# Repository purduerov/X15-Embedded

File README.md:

# X15-Embedded

Embedded code for the ESCs, solenoids, bricks, and more using CAN communication.

This code is developed with [STM32CubeIDE](https://www.st.com/en/development-tools/stm32cubeide.html)
for the [STM32F042K6T6](https://www.st.com/content/ccc/resource/technical/document/datasheet/52/ad/d0/80/e6/be/40/ad/DM00105814.pdf/files/DM00105814.pdf/jcr:content/translations/en.DM00105814.pdf).
See the [F0 reference manual](https://www.st.com/resource/en/reference_manual/dm00031936-stm32f0x1stm32f0x2stm32f0x8-advanced-armbased-32bit-mcus-stmicroelectronics.pdf) too.

## Building and generating code
Driver code is not tracked by git. To get it, open the IOC file for the project
and go to Project > Generate Code. This will produce the appropriate Driver/ folders
for the code.

## More info
See the [References folder](References) for information on usual setups and
the [common folder](common) for information on setting up the shared implementations
and the shared source files themselves. The [Python folder](Python) has code for testing
and a guide for doing so.

### Recommended settings
##### Optimization
Set optimization for Release builds to -03 rather than -Osize (the default). This setting is in
Project > Properties > C/C++ Build > Settings > Tool Settings > MCU GCC Compiler > Optimization.
This should only be done for Release builds. Debug builds should not be optimization

##### Whitespace
In Window > Preferences > C/C++ > Editor > Save Actions
* Check "Remove trailing whitespace"
* Select the "In all lines"
* Check "Ensure newline at the end of file"

This makes it easier to diff files in git and prevent unnecessary changes.

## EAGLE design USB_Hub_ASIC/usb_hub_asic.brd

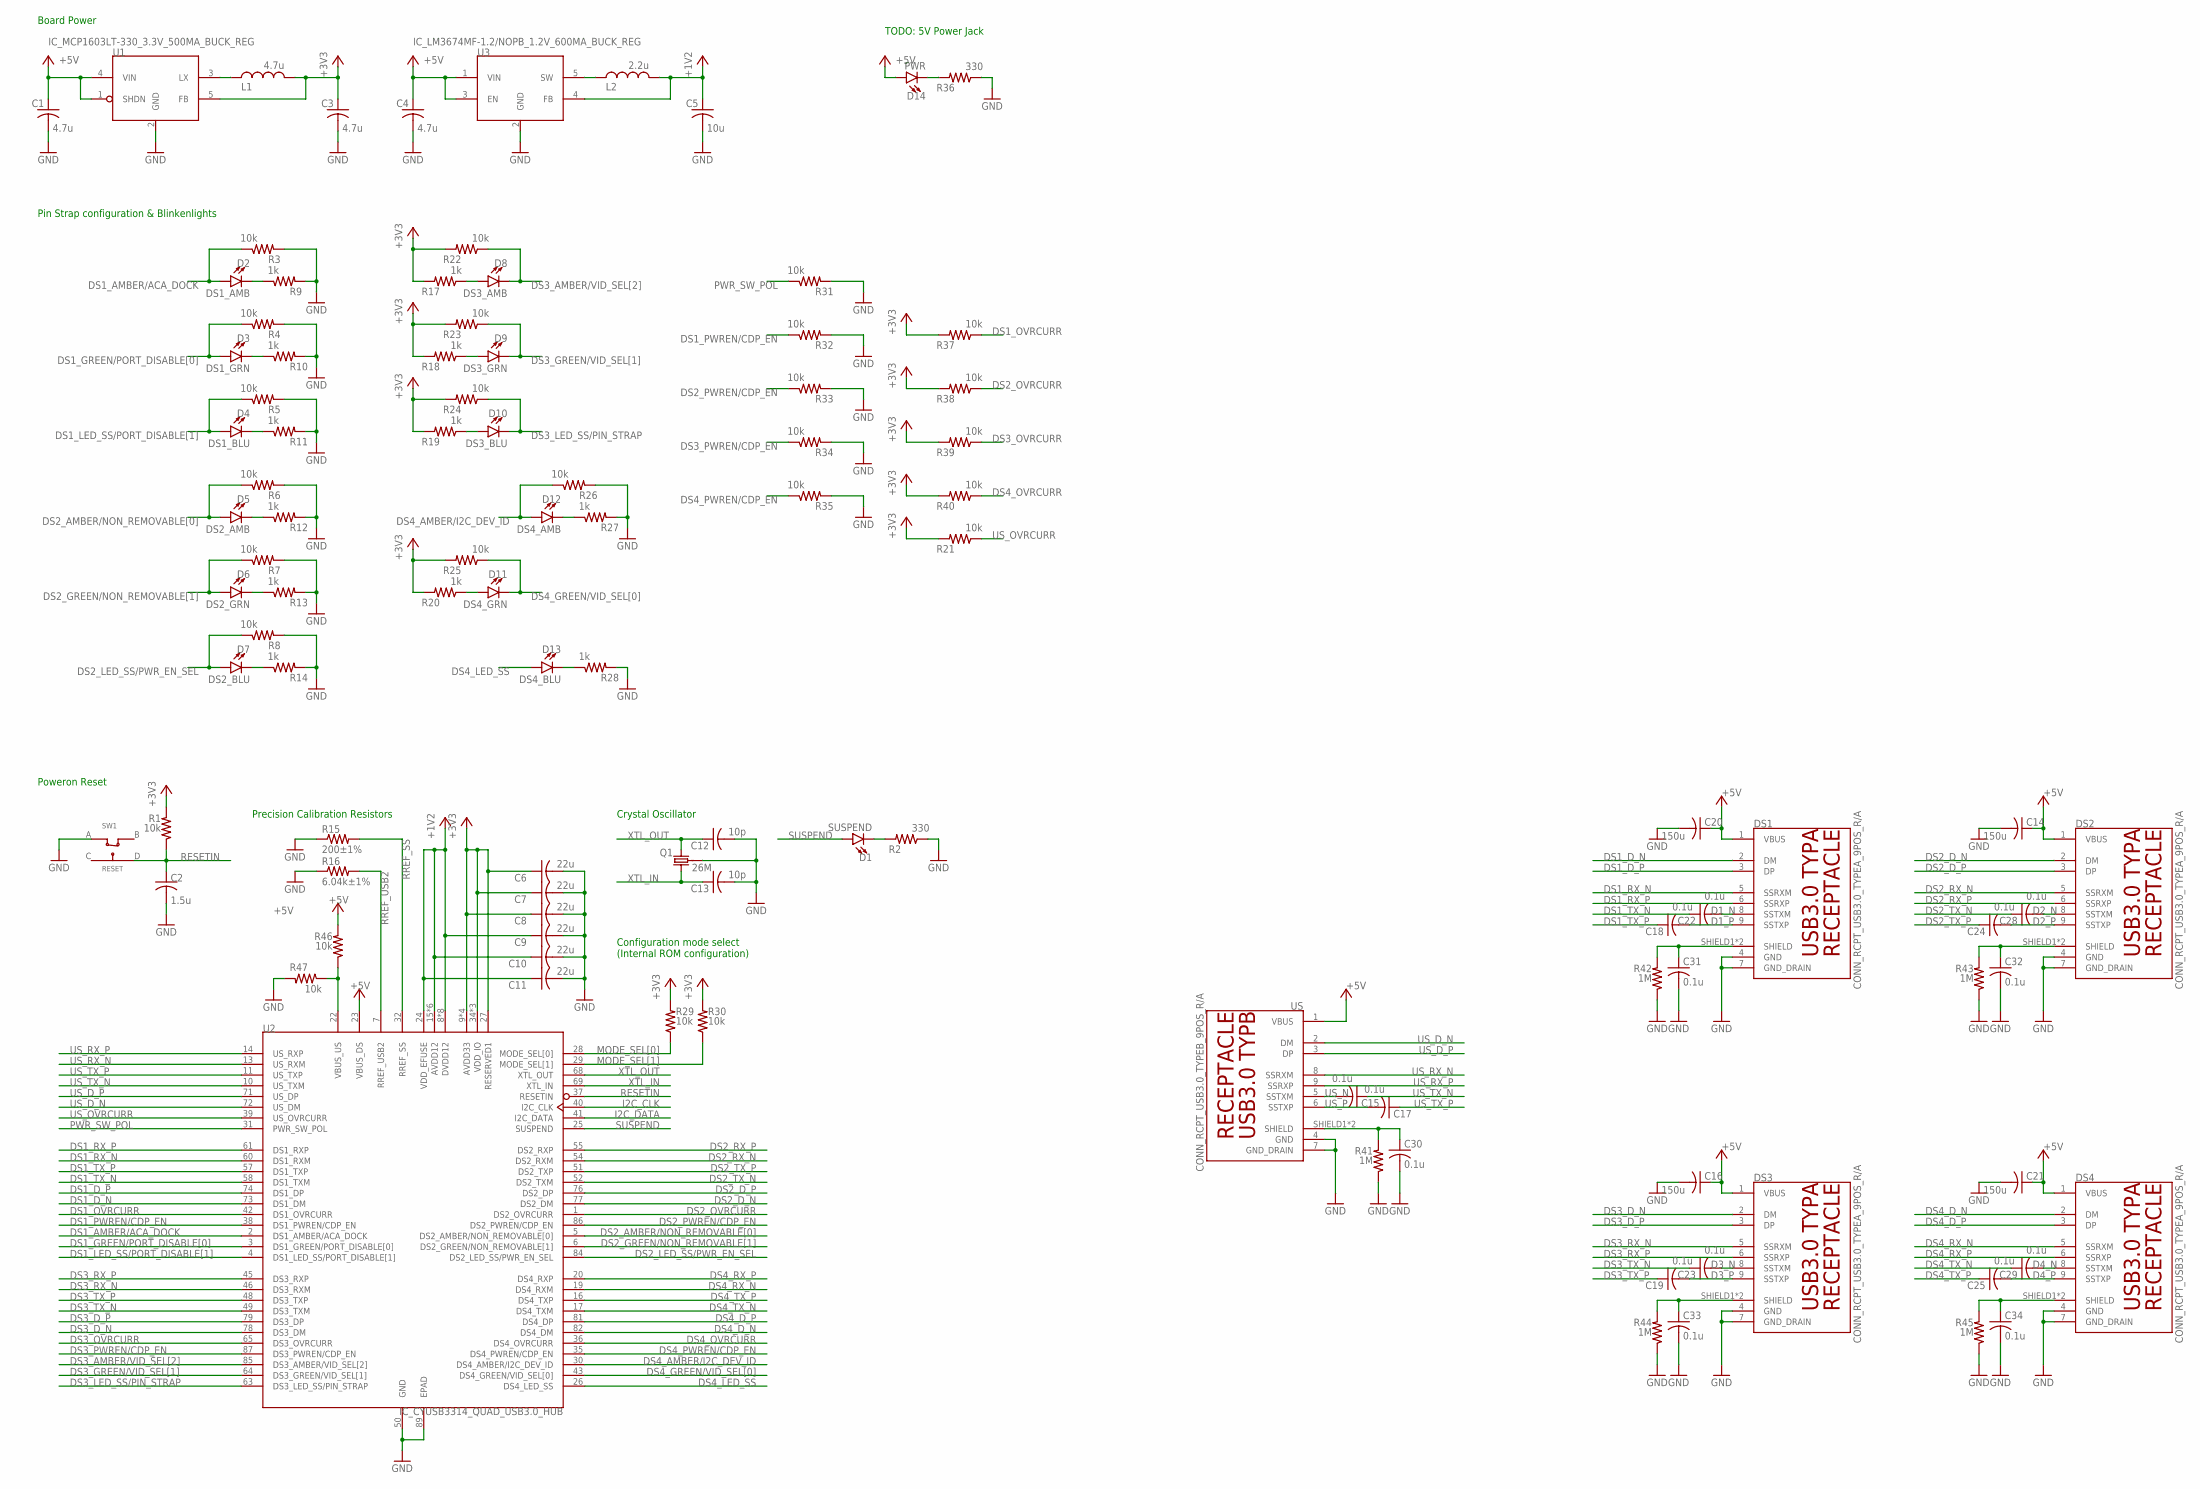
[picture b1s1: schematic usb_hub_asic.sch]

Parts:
C1, C3, C4: 4.7u; C0603
C2: 1.5u; C0603
C5: 10u; C0805
C6, C7, C8, C9, C10, C11: 22u; C0603
C12, C13: 10p; C0603
C14, C16, C20, C21: 150u; C1210K
C15, C17, C18, C19, C22, C23, C24, C25, C28, C29, C30, C31, C32, C33, C34: 0.1u; C0603
D1: SUSPEND; LED-1206
D2: DS1_AMB; LED-1206
D3: DS1_GRN; LED-1206
D4: DS1_BLU; LED-1206
D5: DS2_AMB; LED-1206
D6: DS2_GRN; LED-1206
D7: DS2_BLU; LED-1206
D8: DS3_AMB; LED-1206
D9: DS3_GRN; LED-1206
D10: DS3_BLU; LED-1206
D11: DS4_GRN; LED-1206
D12: DS4_AMB; LED-1206
D13: DS4_BLU; LED-1206
D14: PWR; LED-1206
DS1, DS2, DS3, DS4: CONN_RCPT_USB3.0_TYPEA_9POS_R/A; CONN_RCPT_USB3.0_UJ3-AH-4-TH
L1: 4.7u; SMD-1212(3030METRIC)
L2: 2.2u; SMD-0805(2012METRIC)
Q1: 26M; 4-SMD-ECS-260-13-42-CKM-TR
R1, R3, R4, R5, R6, R7, R8, R21, R22, R23, R24, R25, R26, R29, R30, R31, R32, R33, R34, R35, R37, R38, R39, R40, R46, R47: 10k; R0603
R2, R36: 330; R0603
R9, R10, R11, R12, R13, R14, R17, R18, R19, R20, R27, R28: 1k; R0603
R15: 200±1%; R0603
R16: 6.04k±1%; R0603
R41, R42, R43, R44, R45: 1M; R0603
SW1: RESET; SMD-TLSMDT3C020GLFS
U1: IC_MCP1603LT-330_3.3V_500MA_BUCK_REG; 5-TSOT23
U2: IC_CYUSB3314_QUAD_USB3.0_HUB; 88-QFN_10X10X1_5.3_TPAD
U3: IC_LM3674MF-1.2/NOPB_1.2V_600MA_BUCK_REG; 5-TSOT23
US: CONN_RCPT_USB3.0_TYPEB_9POS_R/A; CONN_RCPT_USB3.0_E8199-030-03

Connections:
+1V2: C5.1, C9.1, C10.1, C11.1, L2.P$2 (2), U2.8 (DVDD12), U2.12 (DVDD12), U2.15 (AVDD12), U2.18 (DVDD12), U2.21 (AVDD12), U2.24 (VDD_EFUSE), U2.33 (DVDD12), U2.44 (AVDD12), U2.47 (DVDD12), U2.53 (DVDD12), U2.56 (AVDD12), U2.59 (DVDD12), U2.62 (AVDD12), U2.67 (AVDD12), U2.83 (DVDD12), U3.4 (FB)
+3V3: C3.1, C6.1, C7.1, C8.1, L1.P$2 (2), R1.2, R17.2, R18.2, R19.2, R20.2, R21.2, R22.2, R23.2, R24.2, R25.2, R29.2, R30.2, R37.2, R38.2, R39.2, R40.2, U1.5 (FB), U2.9 (AVDD33), U2.27 (RESERVED1), U2.34 (VDD_IO), U2.66 (VDD_IO), U2.70 (AVDD33), U2.75 (AVDD33), U2.80 (AVDD33), U2.88 (VDD_IO)
+5V: C1.1, C4.1, C14.1, C16.1, C20.1, C21.1, D14.A, DS1.1 (VBUS), DS2.1 (VBUS), DS3.1 (VBUS), DS4.1 (VBUS), R46.2, U1.1 (SHDN), U1.4 (VIN), U2.23 (VBUS_DS), U3.1 (VIN), U3.3 (EN), US.1 (VBUS)
D1_N: C22.2, DS1.8 (SSTXM)
D1_P: C18.2, DS1.9 (SSTXP)
D2_N: C28.2, DS2.8 (SSTXM)
D2_P: C24.2, DS2.9 (SSTXP)
D3_N: C23.2, DS3.8 (SSTXM)
D3_P: C19.2, DS3.9 (SSTXP)
D4_N: C29.2, DS4.8 (SSTXM)
D4_P: C25.2, DS4.9 (SSTXP)
DS1_AMBER/ACA_DOCK: D2.A, R3.1, U2.2 (DS1_AMBER/ACA_DOCK)
DS1_D_N: DS1.2 (DM), U2.73 (DS1_DM)
DS1_D_P: DS1.3 (DP), U2.74 (DS1_DP)
DS1_GREEN/PORT_DISABLE[0]: D3.A, R4.1, U2.3 (DS1_GREEN/PORT_DISABLE[0])
DS1_LED_SS/PORT_DISABLE[1]: D4.A, R5.1, U2.4 (DS1_LED_SS/PORT_DISABLE[1])
DS1_OVRCURR: R37.1, U2.42 (DS1_OVRCURR)
DS1_PWREN/CDP_EN: R32.1, U2.38 (DS1_PWREN/CDP_EN)
DS1_RX_N: DS1.5 (SSRXM), U2.60 (DS1_RXM)
DS1_RX_P: DS1.6 (SSRXP), U2.61 (DS1_RXP)
DS1_TX_N: C22.1, U2.58 (DS1_TXM)
DS1_TX_P: C18.1, U2.57 (DS1_TXP)
DS2_AMBER/NON_REMOVABLE[0]: D5.A, R6.1, U2.5 (DS2_AMBER/NON_REMOVABLE[0])
DS2_D_N: DS2.2 (DM), U2.77 (DS2_DM)
DS2_D_P: DS2.3 (DP), U2.76 (DS2_DP)
DS2_GREEN/NON_REMOVABLE[1]: D6.A, R7.1, U2.6 (DS2_GREEN/NON_REMOVABLE[1])
DS2_LED_SS/PWR_EN_SEL: D7.A, R8.1, U2.84 (DS2_LED_SS/PWR_EN_SEL)
DS2_OVRCURR: R38.1, U2.1 (DS2_OVRCURR)
DS2_PWREN/CDP_EN: R33.1, U2.86 (DS2_PWREN/CDP_EN)
DS2_RX_N: DS2.5 (SSRXM), U2.54 (DS2_RXM)
DS2_RX_P: DS2.6 (SSRXP), U2.55 (DS2_RXP)
DS2_TX_N: C28.1, U2.52 (DS2_TXM)
DS2_TX_P: C24.1, U2.51 (DS2_TXP)
DS3_AMBER/VID_SEL[2]: D8.C, R22.1, U2.85 (DS3_AMBER/VID_SEL[2])
DS3_D_N: DS3.2 (DM), U2.78 (DS3_DM)
DS3_D_P: DS3.3 (DP), U2.79 (DS3_DP)
DS3_GREEN/VID_SEL[1]: D9.C, R23.1, U2.64 (DS3_GREEN/VID_SEL[1])
DS3_LED_SS/PIN_STRAP: D10.C, R24.1, U2.63 (DS3_LED_SS/PIN_STRAP)
DS3_OVRCURR: R39.1, U2.65 (DS3_OVRCURR)
DS3_PWREN/CDP_EN: R34.1, U2.87 (DS3_PWREN/CDP_EN)
DS3_RX_N: DS3.5 (SSRXM), U2.46 (DS3_RXM)
DS3_RX_P: DS3.6 (SSRXP), U2.45 (DS3_RXP)
DS3_TX_N: C23.1, U2.49 (DS3_TXM)
DS3_TX_P: C19.1, U2.48 (DS3_TXP)
DS4_AMBER/I2C_DEV_ID: D12.A, R26.1, U2.30 (DS4_AMBER/I2C_DEV_ID)
DS4_D_N: DS4.2 (DM), U2.82 (DS4_DM)
DS4_D_P: DS4.3 (DP), U2.81 (DS4_DP)
DS4_GREEN/VID_SEL[0]: D11.C, R25.1, U2.43 (DS4_GREEN/VID_SEL[0])
DS4_LED_SS: D13.A, U2.26 (DS4_LED_SS)
DS4_OVRCURR: R40.1, U2.36 (DS4_OVRCURR)
DS4_PWREN/CDP_EN: R35.1, U2.35 (DS4_PWREN/CDP_EN)
DS4_RX_N: DS4.5 (SSRXM), U2.19 (DS4_RXM)
DS4_RX_P: DS4.6 (SSRXP), U2.20 (DS4_RXP)
DS4_TX_N: C29.1, U2.17 (DS4_TXM)
DS4_TX_P: C25.1, U2.16 (DS4_TXP)
GND: C1.2, C2.2, C3.2, C4.2, C5.2, C6.2, C7.2, C8.2, C9.2, C10.2, C11.2, C12.2, C13.2, C14.2, C16.2, C20.2, C21.2, C30.2, C31.2, C32.2, C33.2, C34.2, DS1.4 (GND), DS1.7 (GND_DRAIN), DS2.4 (GND), DS2.7 (GND_DRAIN), DS3.4 (GND), DS3.7 (GND_DRAIN), DS4.4 (GND), DS4.7 (GND_DRAIN), Q1.P$2 (GND), Q1.P$4 (GND), R2.1, R3.2, R4.2, R5.2, R6.2, R7.2, R8.2, R9.2, R10.2, R11.2, R12.2, R13.2, R14.2, R15.1, R16.1, R26.2, R27.2, R28.2, R31.2, R32.2, R33.2, R34.2, R35.2, R36.1, R41.1, R42.1, R43.1, R44.1, R45.1, R47.2, SW1.A, U1.2 (GND), U2.50 (GND), U2.89 (EPAD), U3.2 (GND), US.4 (GND), US.7 (GND_DRAIN)
I2C_CLK: U2.40 (I2C_CLK)
I2C_DATA: U2.41 (I2C_DATA)
MODE_SEL[0]: R29.1, U2.28 (MODE_SEL[0])
MODE_SEL[1]: R30.1, U2.29 (MODE_SEL[1])
unnamed: D1.C, R2.2
unnamed: D14.C, R36.2
unnamed: D2.C, R9.1
unnamed: D5.C, R12.1
unnamed: D3.C, R10.1
unnamed: D6.C, R13.1
unnamed: D4.C, R11.1
unnamed: D7.C, R14.1
unnamed: D10.A, R19.1
unnamed: D9.A, R18.1
unnamed: D8.A, R17.1
unnamed: D12.C, R27.1
unnamed: L2.P$1 (1), U3.5 (SW)
unnamed: D13.C, R28.1
unnamed: L1.P$1 (1), U1.3 (LX)
unnamed: D11.A, R20.1
unnamed: R46.1, R47.1, U2.22 (VBUS_US)
unnamed: C30.1, R41.2, US.SHIELD1 (SHIELD), US.SHIELD2 (SHIELD)
unnamed: C31.1, DS1.SHIELD1 (SHIELD), DS1.SHIELD2 (SHIELD), R42.2
unnamed: C32.1, DS2.SHIELD1 (SHIELD), DS2.SHIELD2 (SHIELD), R43.2
unnamed: C33.1, DS3.SHIELD1 (SHIELD), DS3.SHIELD2 (SHIELD), R44.2
unnamed: C34.1, DS4.SHIELD1 (SHIELD), DS4.SHIELD2 (SHIELD), R45.2
PWR_SW_POL: R31.1, U2.31 (PWR_SW_POL)
RESETIN: C2.1, R1.1, SW1.D, U2.37 (RESETIN)
RREF_SS: R15.2, U2.32 (RREF_SS)
RREF_USB2: R16.2, U2.7 (RREF_USB2)
SUSPEND: D1.A, U2.25 (SUSPEND)
US_D_N: U2.72 (US_DM), US.2 (DM)
US_D_P: U2.71 (US_DP), US.3 (DP)
US_N: C15.2, US.5 (SSTXM)
US_OVRCURR: R21.1, U2.39 (US_OVRCURR)
US_P: C17.2, US.6 (SSTXP)
US_RX_N: U2.13 (US_RXM), US.8 (SSRXM)
US_RX_P: U2.14 (US_RXP), US.9 (SSRXP)
US_TX_N: C15.1, U2.10 (US_TXM)
US_TX_P: C17.1, U2.11 (US_TXP)
XTL_IN: C13.1, Q1.P$1 (1), U2.69 (XTL_IN)
XTL_OUT: C12.1, Q1.P$3 (2), U2.68 (XTL_OUT)

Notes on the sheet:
Precision Calibration Resistors
Poweron Reset
Configuration mode select (Internal ROM configuration)
Crystal Oscillator
Pin Strap configuration & Blinkenlights
Board Power
TODO: 5V Power Jack

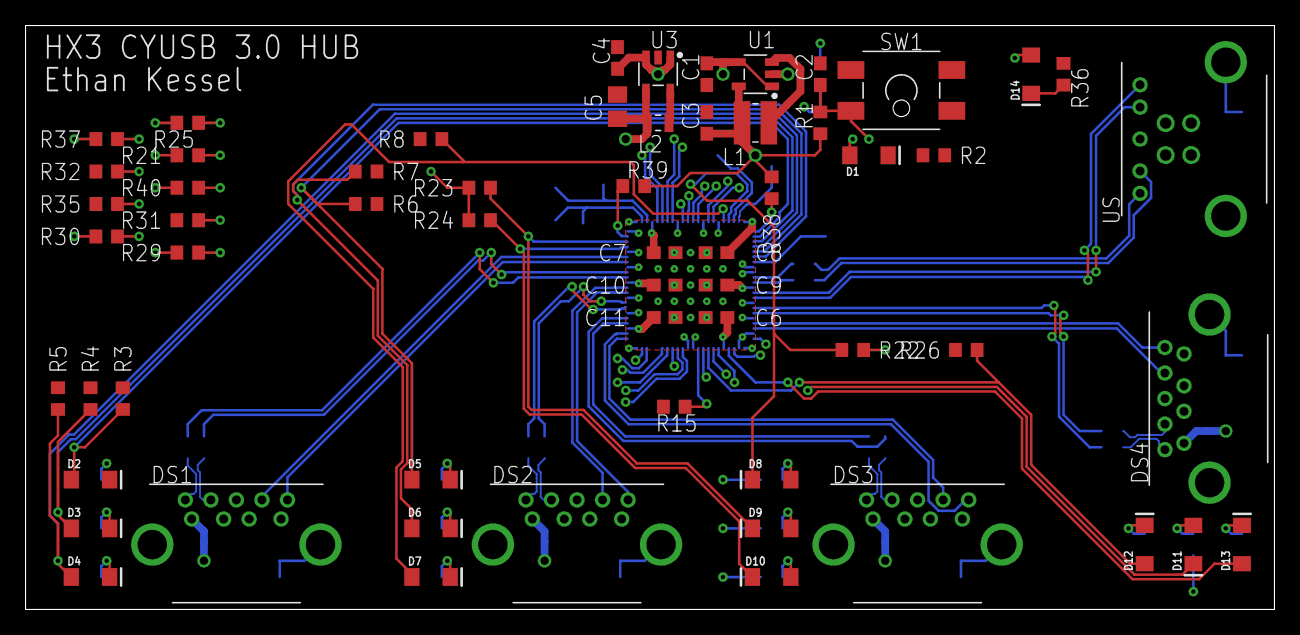
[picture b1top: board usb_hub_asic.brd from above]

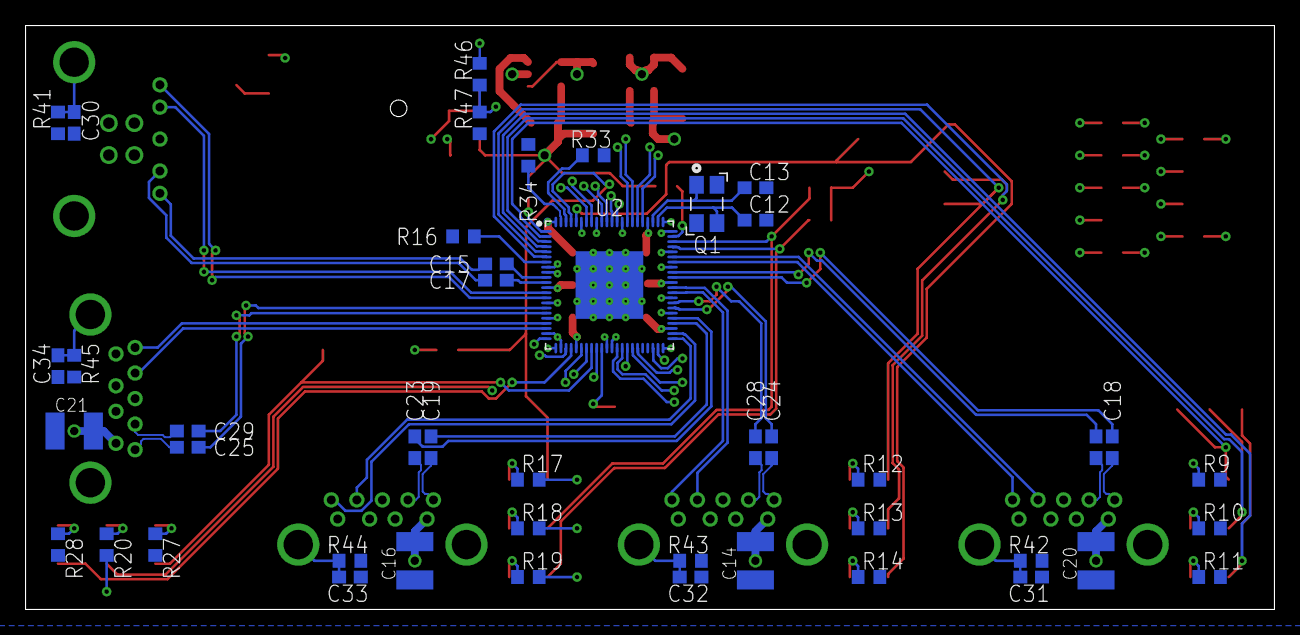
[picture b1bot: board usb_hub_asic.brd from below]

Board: 4 copper layers, 97.8 x 45.7 mm, 105 parts (45 on the bottom side), 96 nets.

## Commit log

2022-09-14 pushed forward from X14-Embedded
2022-09-15 Added a new project for ESC
    Read the Summary
2022-09-17 haha
    ahah
2022-09-17 changed folder name
2022-09-17 stuff
2022-09-17 hahahahahaha
    i deleted and cleaned
2022-09-17 New project with folder
    I made a new Project called CodeBaseESC
2022-09-17 Not many significant changes
    read title
2022-09-24 Added logic to get read the timer differnce between 2 pwm signals
2022-10-06 Got the interupt trigger to work
    haha
2022-10-13 Starting work on USB Hub ASIC schematic design.
2022-10-13 This does not work
    Haha i am sad
2022-10-15 Basic CYUSB3314 connections started
2022-10-15 Added Serial Monitor
    We can now debug. Yay
2022-10-20 USB port connections and CYUSB3314 decoupling considerations
2022-10-22 Reverting back to normal
2022-10-22 Hub configuration straps, LEDs, WIP power
2022-10-22 updates for 10/22
2022-10-27 Preliminary Design Review Pre-Baseline
2022-10-29 Added noise smoothing and now need to rework clock
    Will change clock based on what raghav sent in slack yesterday.
2022-11-05 Post design review warning approval
2022-11-05 Reset the register using the interupt and it works better
2022-11-17 moving forward with pcb design
2022-11-19 Power plane routing for chip
2022-12-01 Component selection and a bit more placement
2022-12-08 Board layout, need to place config resistors
2022-12-08 more hectic routing
2022-12-11 start over on board design w/ 4 layers
2023-01-14 routing is hard
2023-01-22 ROUTING IS DONE?
2023-05-14 This goes on the nucleo that takes SPI from the PI and outputs the correct pwm

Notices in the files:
parts and their libraries:
SparkFun-LED: Licensing: Creative Commons ShareAlike 4.0 International - https://creativecommons.org/licenses/by-sa/4.0
